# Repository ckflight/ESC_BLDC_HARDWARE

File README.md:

# BLHELI_S Electronic Speed Controller Hardware Design

#### ESC Information:

 * BLDC 3 phase motor speed controller hardware design working with open source BLHeli_S C configuration firmware C_H_30.

 * The ESC is tested on a real quadcopter with brushless motors at 40 Ampere current rating. 
 
 * TPN2R703NL Power MOSFETs are used on this design, which are capable of delivering current up to 45 Ampere for normal operation and 90 Ampere peak for short pulse.
 
 * MP1907 High Frequency Half Bridge Gate driver is used for controlling the Power MOSFETs. High power MOSFET transistors have high Q and capacitance values. To open the gate it requires high amount of current in short amount of time where current requirement decreases exponentially. This is the reason for using a Gate Driver. Also an extra gate resistor is populated at the input of MOSFET gate pin.
 
 $$ Igate(max) = {Vgate \over Rgate} $$

        4S Lipo Battery Vgate = 16V, Rgate = 10 Ohm and Igate(max) = 1.5A
 
 $$ Igate = {Qfet \over Tswitch} $$
 
         For a MOSFET with Qtotal = 50nC Tswtich = 500nS and Igate(needed) = 0.1A.
         Therefore, a 100 Ohm gate resistor is populated.

 * Phase C has current bar trace. Or it can be done with extra solder on the trace.

# BLHELI_S Firmware Flashing Guide

When esc is new assembled the EFM8BB2 does not have BLHeli_S Bootloader.
For the first time flashing, 4wire interface is used by using C2CK, C2D, 3.3v and GND pins where it will load both bootloader and firmware to esc.
After this step, esc can be flashed with 1-Wire interface (Esc's pwm pin).

####Flashing ESC for the first time.

1. Open "Make interfaces" section
2. Select the Arduino board that will be used as programmer.
3. Click "Arduino 4way-interface" and flash it to arduino.
   (Now arduino became a 4wire programmer)

4. Select "SILABS C2 (4way if)"
5. Connect Arduino to Custom ESC
       GND to GND 
       3.3v to 3.3v
       Arduino Pin12 to C2D 
       Arduino Pin11 to C2CK
6. Open ESC Setup section and connect to esc and click Flash BLHeli
   (choose suitable version, my custom quadcopter esc v2 is working with C type)

Now the esc is both flashed with blheli bootloader and the blheli firmware, 
therefore 1wire interface can be used which is the esc's pwm pin. 
Or flight controller can be used in passthrough mode.

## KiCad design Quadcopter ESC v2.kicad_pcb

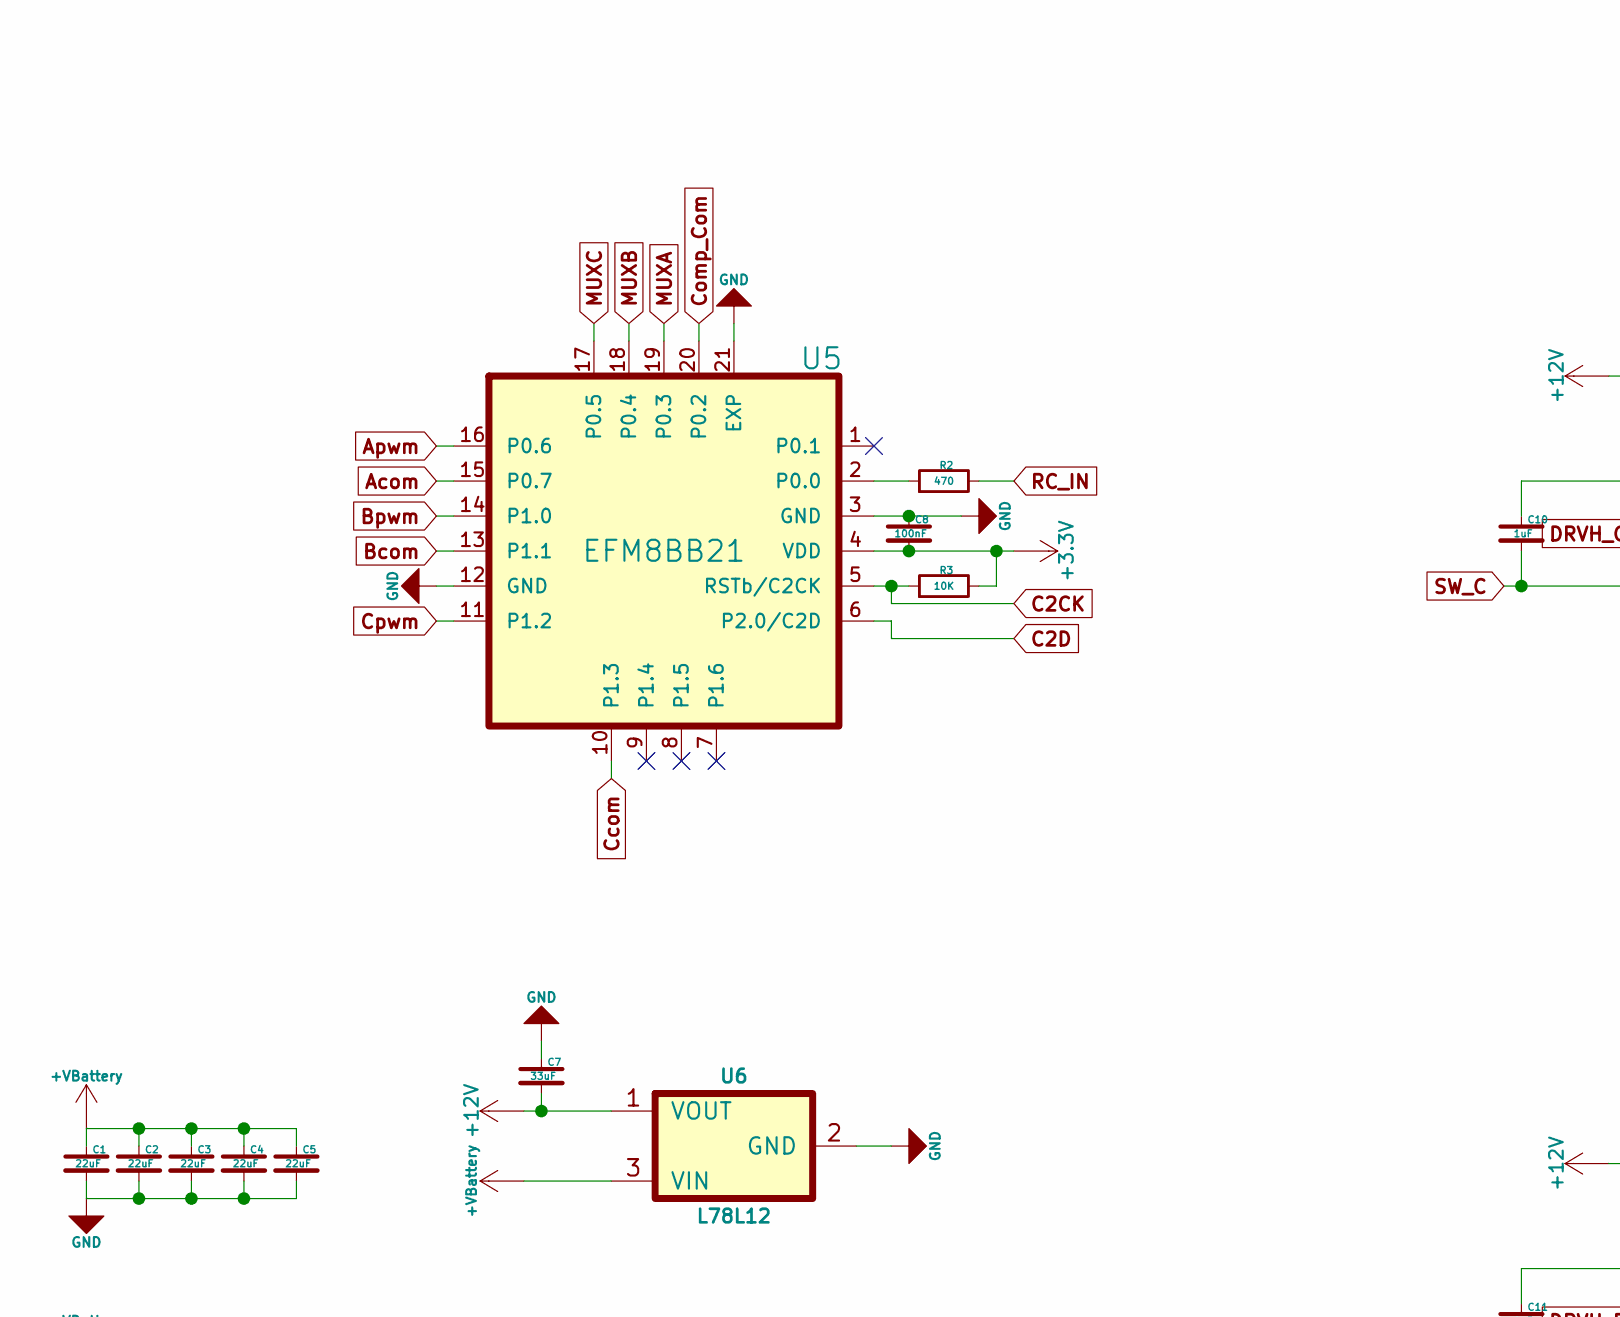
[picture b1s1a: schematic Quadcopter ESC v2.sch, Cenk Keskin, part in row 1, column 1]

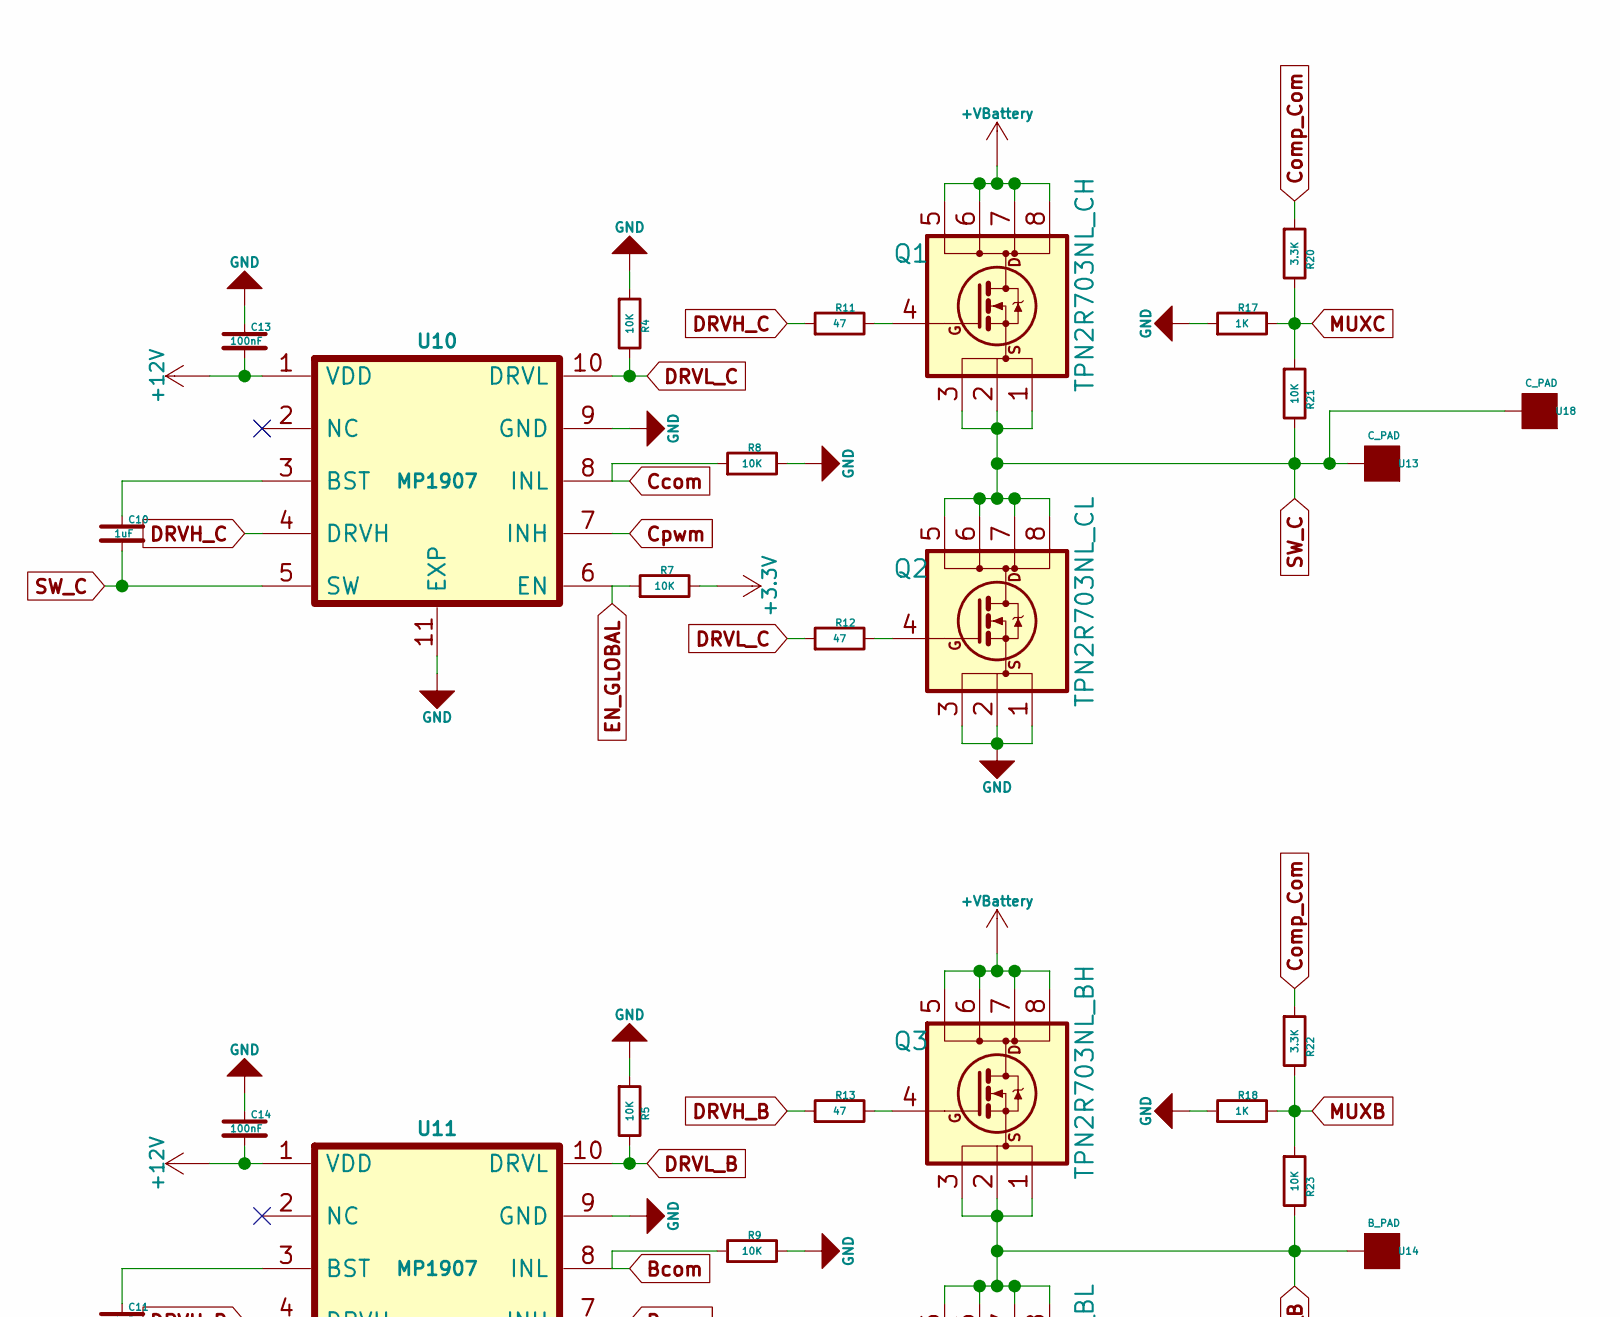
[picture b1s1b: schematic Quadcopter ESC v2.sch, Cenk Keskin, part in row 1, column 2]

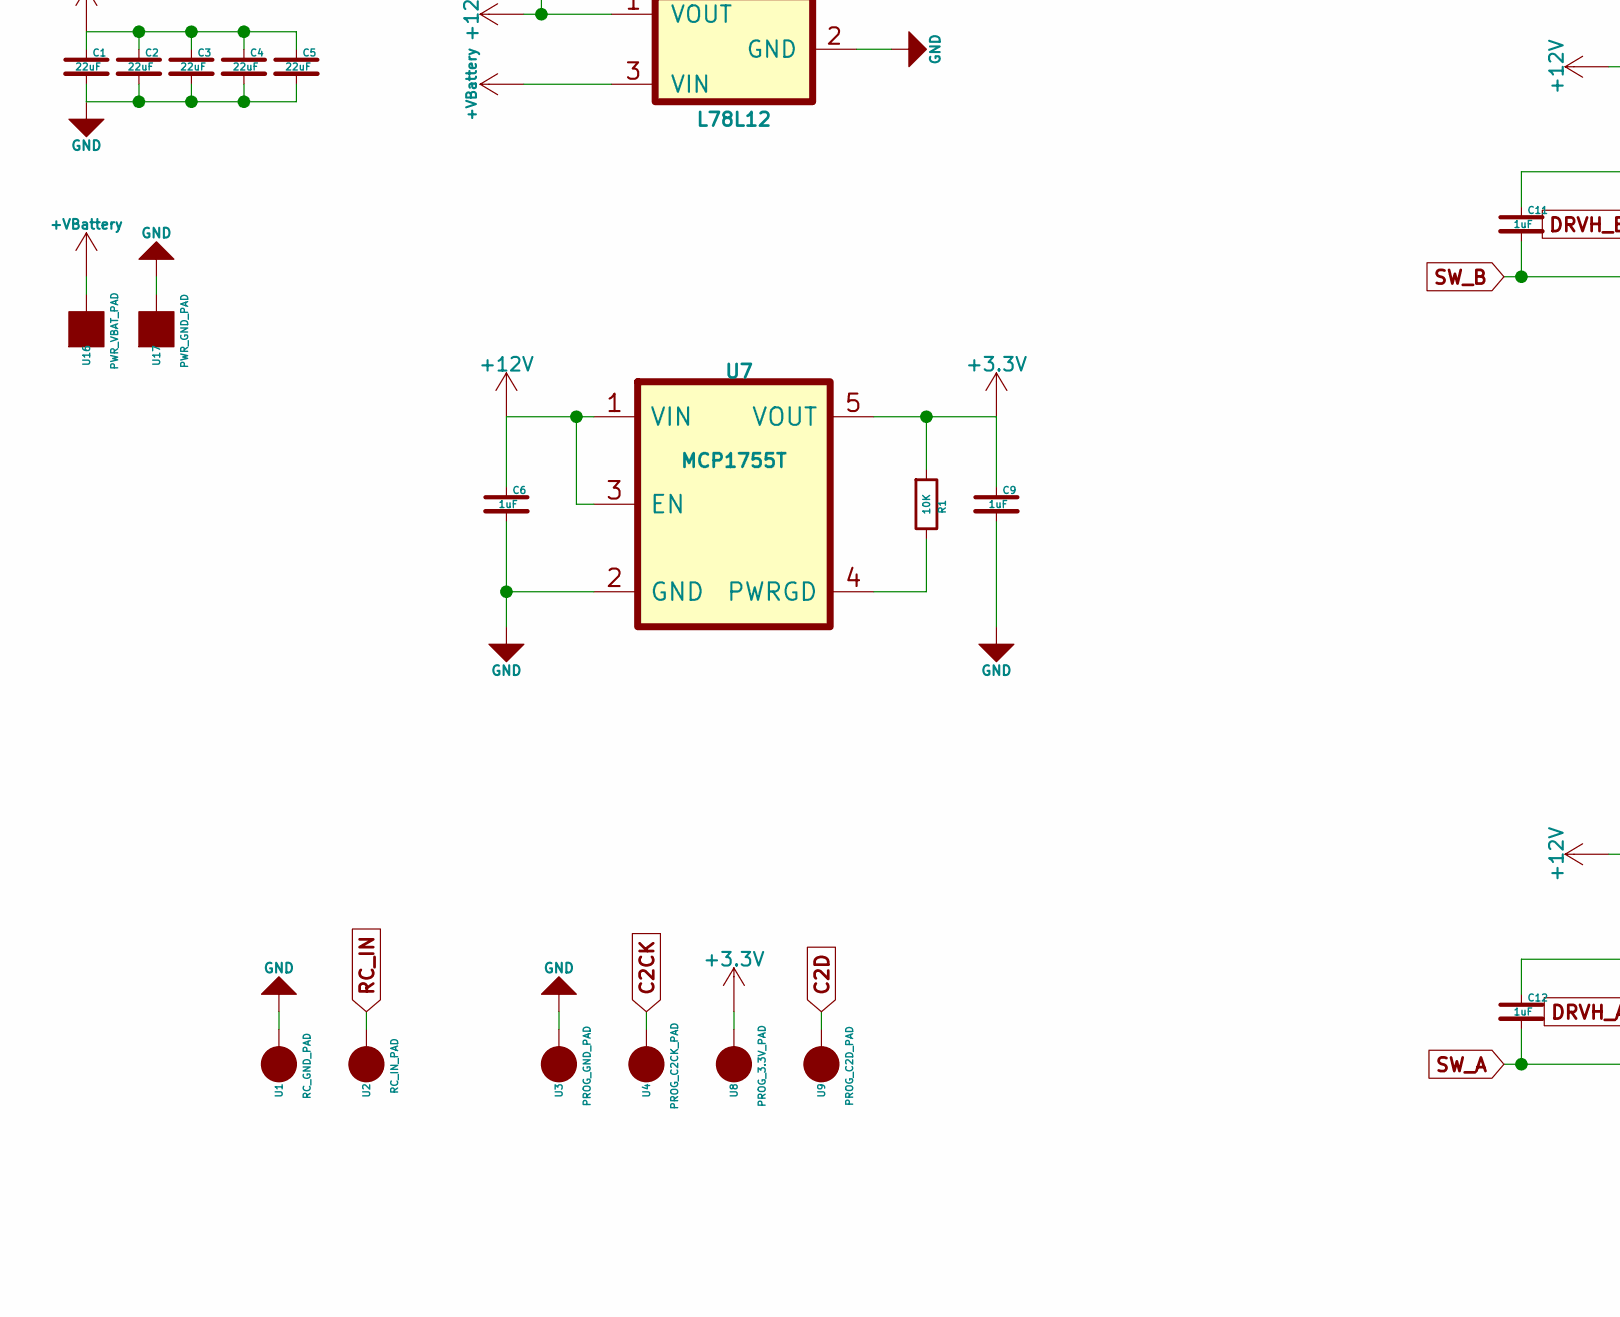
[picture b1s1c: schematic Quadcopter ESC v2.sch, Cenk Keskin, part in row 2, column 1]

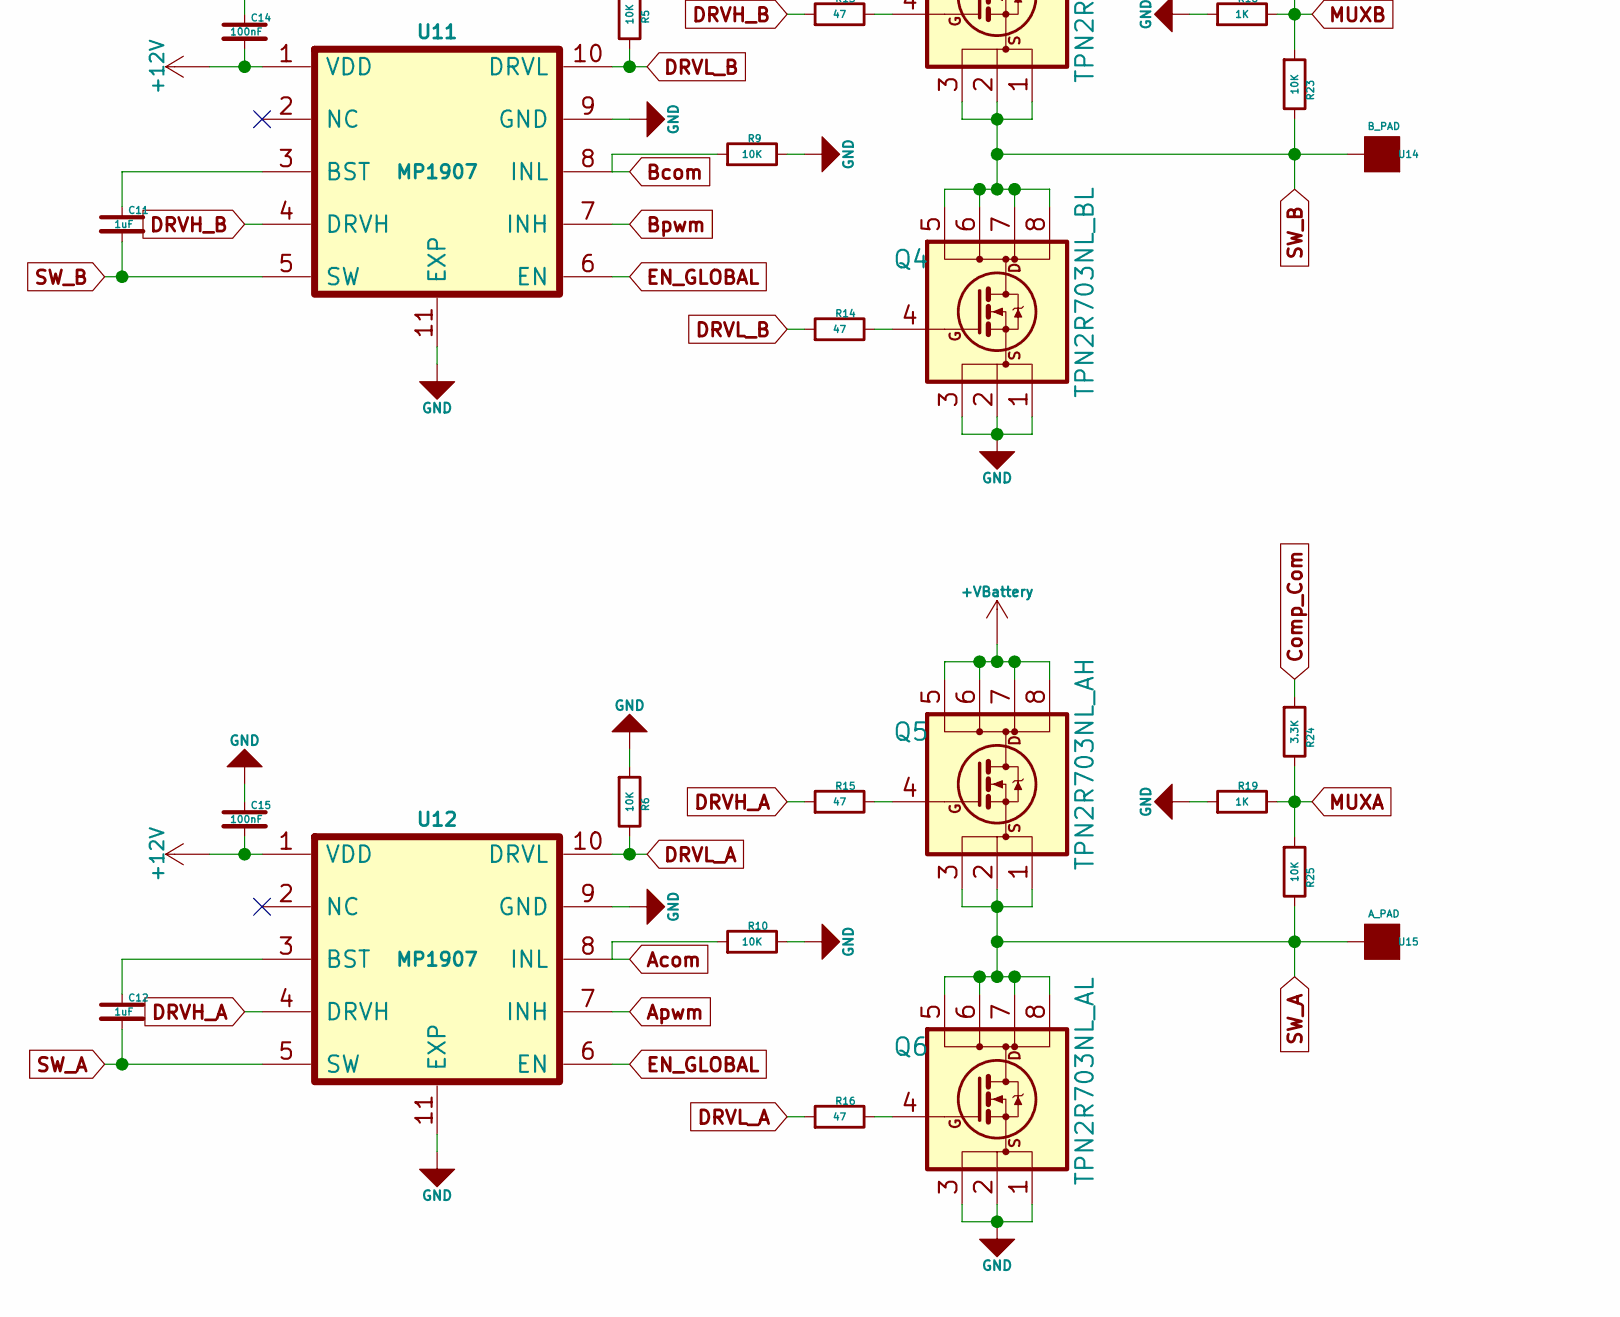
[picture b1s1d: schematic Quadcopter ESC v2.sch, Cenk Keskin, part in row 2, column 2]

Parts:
C1, C2, C3, C4, C5: 22uF; SMD_0805
C6, C9, C10, C11, C12: 1uF; SMD_0603
C7: 33uF; SMD_1210
C8, C13, C14, C15: 100nF; SMD_0402
Q1: TPN2R703NL_CH; TSDSON_8
Q2: TPN2R703NL_CL; TSDSON_8
Q3: TPN2R703NL_BH; TSDSON_8
Q4: TPN2R703NL_BL; TSDSON_8
Q5: TPN2R703NL_AH; TSDSON_8
Q6: TPN2R703NL_AL; TSDSON_8
R1, R3, R4, R5, R6, R7, R8, R9, R10, R21, R23, R25: 10K; SMD_0402
R2: 470; SMD_0402
R11, R12, R13, R14, R15, R16: 47; SMD_0402
R17, R18, R19: 1K; SMD_0402
R20, R22, R24: 3.3K; SMD_0402
U1: RC_GND_PAD; SolderPad_1_2x2.5mm_SMD_Oval
U2: RC_IN_PAD; SolderPad_1_2x2.5mm_SMD_Oval
U3: PROG_GND_PAD; SolderPad_1_1.2mm_SMD_Circle
U4: PROG_C2CK_PAD; SolderPad_1_1.2mm_SMD_Circle
U5: EFM8BB21; QFN20_1EXP_3x3mm_Pitch0.5mm
U6: L78L12; SOT89-3
U7: MCP1755T; SOT23_5
U8: PROG_3.3V_PAD; SolderPad_1_1.2mm_SMD_Circle
U9: PROG_C2D_PAD; SolderPad_1_1.2mm_SMD_Circle
U10, U11, U12: MP1907; QFN10_1EXP_3x3mm_Pitch0.5mm
U13: C_PAD; SolderPad_1_2.5mm_SMD_Rectangle
U14: B_PAD; SolderPad_1_2.5mm_SMD_Rectangle
U15: A_PAD; SolderPad_1_2.5mm_SMD_Rectangle
U16: PWR_VBAT_PAD; SolderPad_1_2.5mm_SMD_Rectangle
U17: PWR_GND_PAD; SolderPad_1_2.5mm_SMD_Rectangle
U18: C_PAD; SolderPad_1_1x8mm_SMD_BUSBAR

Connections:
+3V3: C8.2, C9.1, R1.1, R3.2, R7.2, U5.4 (VDD), U7.5 (VOUT), U8.1
+12V: C6.1, C7.2, C13.2, C14.2, C15.2, U6.1 (VOUT), U7.1 (VIN), U7.3 (EN), U10.1 (VDD), U11.1 (VDD), U12.1 (VDD)
+VBattery: C1.1, C2.1, C3.1, C4.1, C5.1, Q1.5 (D), Q1.6 (D), Q1.7 (D), Q1.8 (D), Q3.5 (D), Q3.6 (D), Q3.7 (D), Q3.8 (D), Q5.5 (D), Q5.6 (D), Q5.7 (D), Q5.8 (D), U6.3 (VIN), U16.1
Acom: R10.1, U5.15 (P0.7), U12.8 (INL)
Apwm: U5.16 (P0.6), U12.7 (INH)
Bcom: R9.1, U5.13 (P1.1), U11.8 (INL)
Bpwm: U5.14 (P1.0), U11.7 (INH)
C2CK: R3.1, U4.1, U5.5 (RSTb/C2CK)
C2D: U5.6 (P2.0/C2D), U9.1
Ccom: R8.1, U5.10 (P1.3), U10.8 (INL)
Comp_Com: R20.1, R22.1, R24.1, U5.20 (P0.2)
Cpwm: U5.11 (P1.2), U10.7 (INH)
DRVH_A: R15.1, U12.4 (DRVH)
DRVH_B: R13.1, U11.4 (DRVH)
DRVH_C: R11.1, U10.4 (DRVH)
DRVL_A: R6.2, R16.1, U12.10 (DRVL)
DRVL_B: R5.2, R14.1, U11.10 (DRVL)
DRVL_C: R4.2, R12.1, U10.10 (DRVL)
EN_GLOBAL: R7.1, U10.6 (EN), U11.6 (EN), U12.6 (EN)
GND: C1.2, C2.2, C3.2, C4.2, C5.2, C6.2, C7.1, C8.1, C9.2, C13.1, C14.1, C15.1, Q2.1 (S), Q2.2 (S), Q2.3 (S), Q4.1 (S), Q4.2 (S), Q4.3 (S), Q6.1 (S), Q6.2 (S), Q6.3 (S), R4.1, R5.1, R6.1, R8.2, R9.2, R10.2, R17.1, R18.1, R19.1, U1.1, U3.1, U5.3 (GND), U5.12 (GND), U5.21 (EXP), U6.2 (GND), U7.2 (GND), U10.9 (GND), U10.11 (EXP), U11.9 (GND), U11.11 (EXP), U12.9 (GND), U12.11 (EXP), U17.1
MUXA: R19.2, R24.2, R25.1, U5.19 (P0.3)
MUXB: R18.2, R22.2, R23.1, U5.18 (P0.4)
MUXC: R17.2, R20.2, R21.1, U5.17 (P0.5)
unnamed: C10.1, U10.3 (BST)
unnamed: C11.1, U11.3 (BST)
unnamed: C12.1, U12.3 (BST)
unnamed: Q1.4 (G), R11.2
unnamed: Q2.4 (G), R12.2
unnamed: Q3.4 (G), R13.2
unnamed: Q4.4 (G), R14.2
unnamed: Q5.4 (G), R15.2
unnamed: Q6.4 (G), R16.2
unnamed: R1.2, U7.4 (PWRGD)
unnamed: R2.1, U5.2 (P0.0)
RC_IN: R2.2, U2.1
SW_A: C12.2, Q5.1 (S), Q5.2 (S), Q5.3 (S), Q6.5 (D), Q6.6 (D), Q6.7 (D), Q6.8 (D), R25.2, U12.5 (SW), U15.1
SW_B: C11.2, Q3.1 (S), Q3.2 (S), Q3.3 (S), Q4.5 (D), Q4.6 (D), Q4.7 (D), Q4.8 (D), R23.2, U11.5 (SW), U14.1
SW_C: C10.2, Q1.1 (S), Q1.2 (S), Q1.3 (S), Q2.5 (D), Q2.6 (D), Q2.7 (D), Q2.8 (D), R21.2, U10.5 (SW), U13.1, U18.1

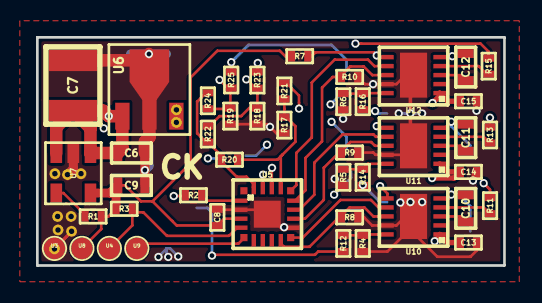
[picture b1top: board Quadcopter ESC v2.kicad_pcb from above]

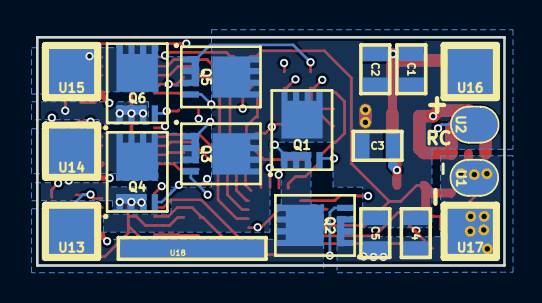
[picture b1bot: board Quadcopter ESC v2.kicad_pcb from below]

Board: 4 copper layers, 26.0 x 12.7 mm, 64 parts (19 on the bottom side), 38 nets.
